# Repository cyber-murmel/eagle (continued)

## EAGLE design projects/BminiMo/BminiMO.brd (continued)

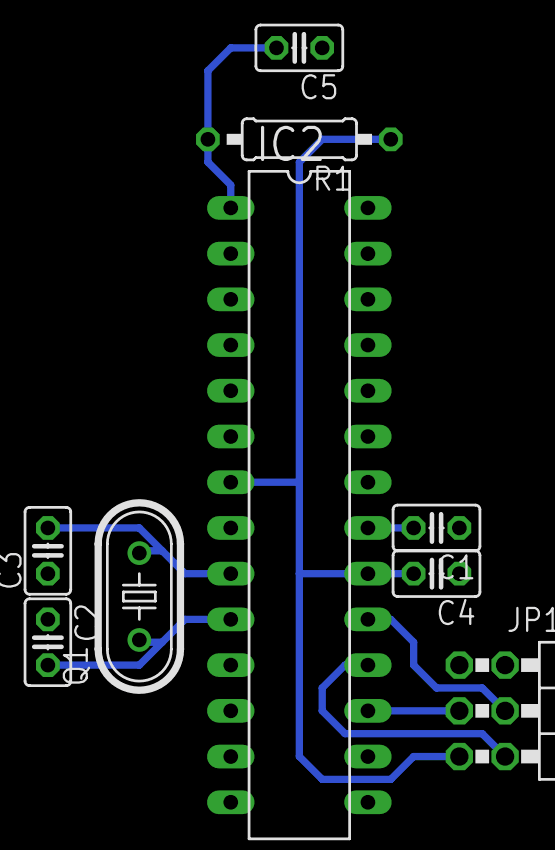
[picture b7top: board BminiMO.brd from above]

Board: 2 copper layers, 9 parts (0 on the bottom side), 9 nets.

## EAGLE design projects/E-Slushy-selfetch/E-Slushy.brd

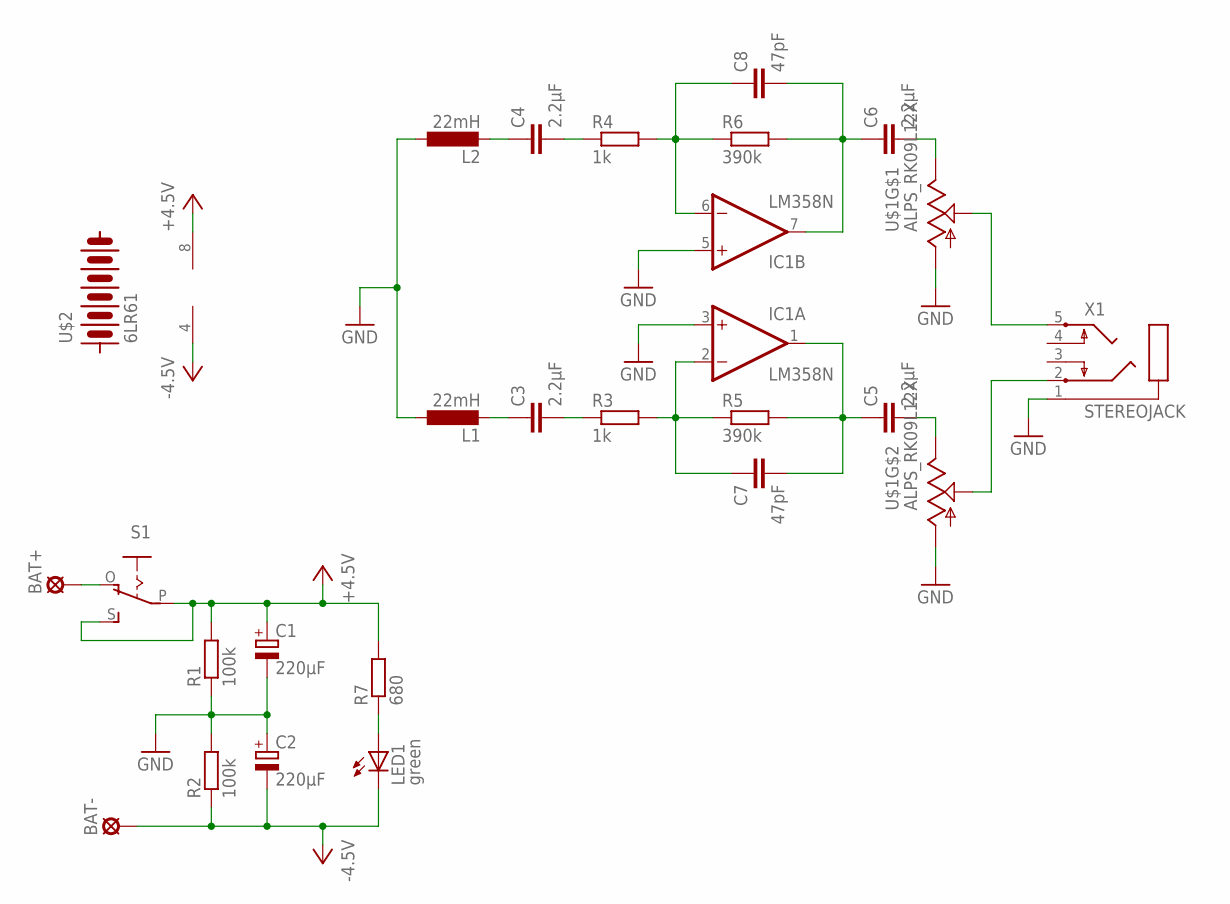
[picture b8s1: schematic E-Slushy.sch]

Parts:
BAT+: SE14
BAT-: SE14
C1, C2: 220μF; PANASONIC_D
C3, C4, C5, C6: 2.2μF; C1206K
C7, C8: 47pF; C1206K
IC1: LM358N; DIL08
L1, L2: 22mH; 6000-XXXX-RC
LED1: green; LED5MM
R1, R2: 100k; R1206
R3, R4: 1k; R1206
R5, R6: 390k; R1206
R7: 680; R1206
S1: EG1218S; EG1218
U$1: ALPS_RK09L12X; RK09L12
U$2: 6LR61
X1: STEREOJACK; STX3100

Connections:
+4.5V: C1.+, IC1.8 (V+), R1.2, R7.2, S1.P, S1.S
-4.5V: BAT-.MP, C2.-, IC1.4 (V-), LED1.K (C), R2.1
GND: C1.-, C2.+, IC1.3 (+IN), IC1.5 (+IN), L1.1, L2.1, R1.1, R2.2, U$1.A1 (1), U$1.B1 (1), X1.1
unnamed: C3.1, L1.2
unnamed: C3.2, R3.1
unnamed: C4.1, L2.2
unnamed: C4.2, R4.1
unnamed: C7.1, IC1.2 (-IN), R3.2, R5.1
unnamed: C5.1, C7.2, IC1.1 (OUT), R5.2
unnamed: C8.1, IC1.6 (-IN), R4.2, R6.1
unnamed: C6.1, C8.2, IC1.7 (OUT), R6.2
unnamed: C5.2, U$1.B3 (3)
unnamed: C6.2, U$1.A3 (3)
unnamed: U$1.B2 (2), X1.2
unnamed: U$1.A2 (2), X1.5
unnamed: BAT+.MP, S1.O
unnamed: LED1.A, R7.1

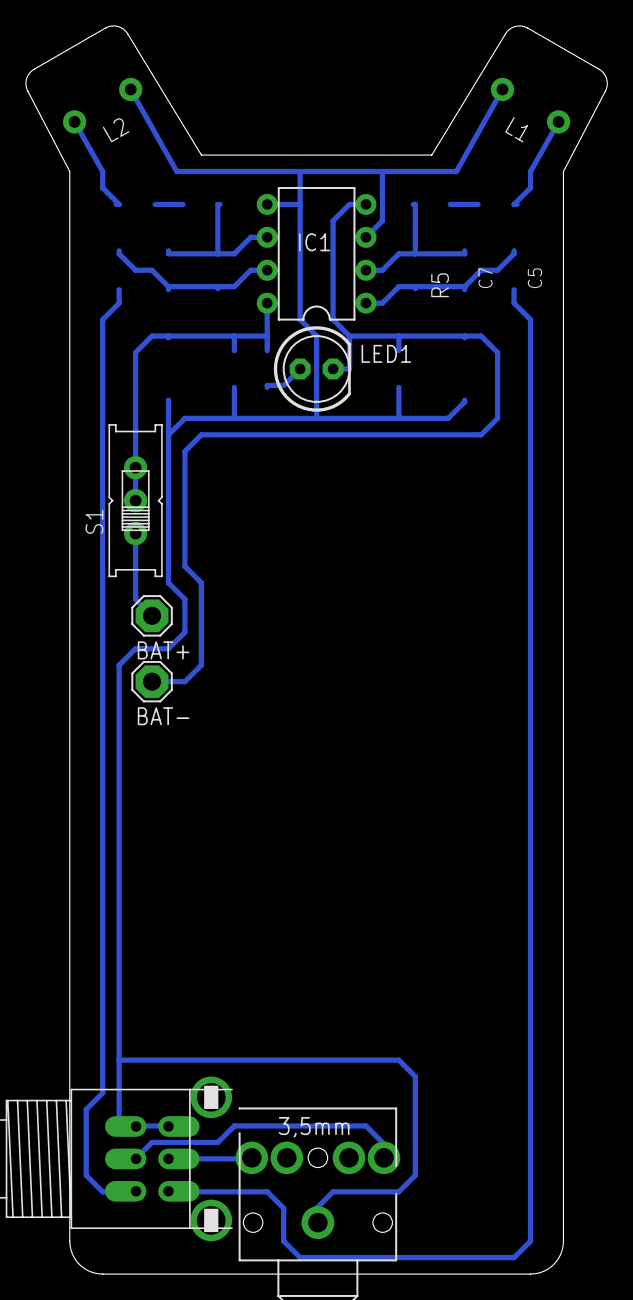
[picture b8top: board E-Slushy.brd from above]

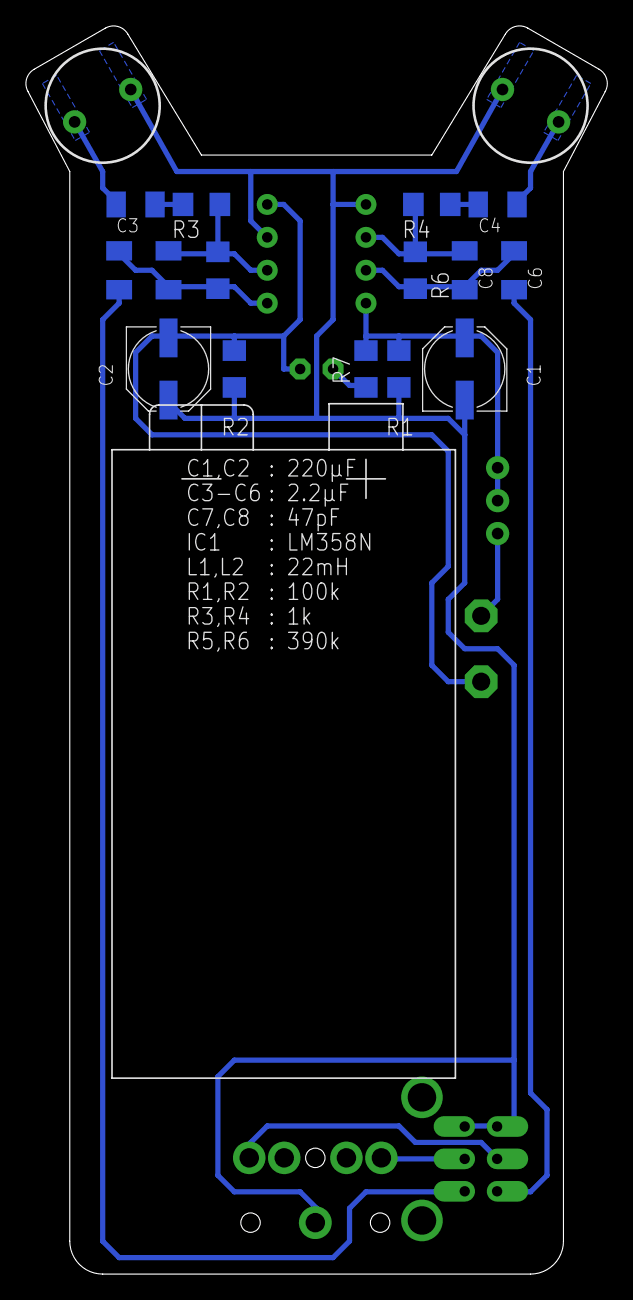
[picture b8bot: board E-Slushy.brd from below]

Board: 2 copper layers, 44.9 x 96.3 mm, 25 parts (18 on the bottom side), 17 nets.
